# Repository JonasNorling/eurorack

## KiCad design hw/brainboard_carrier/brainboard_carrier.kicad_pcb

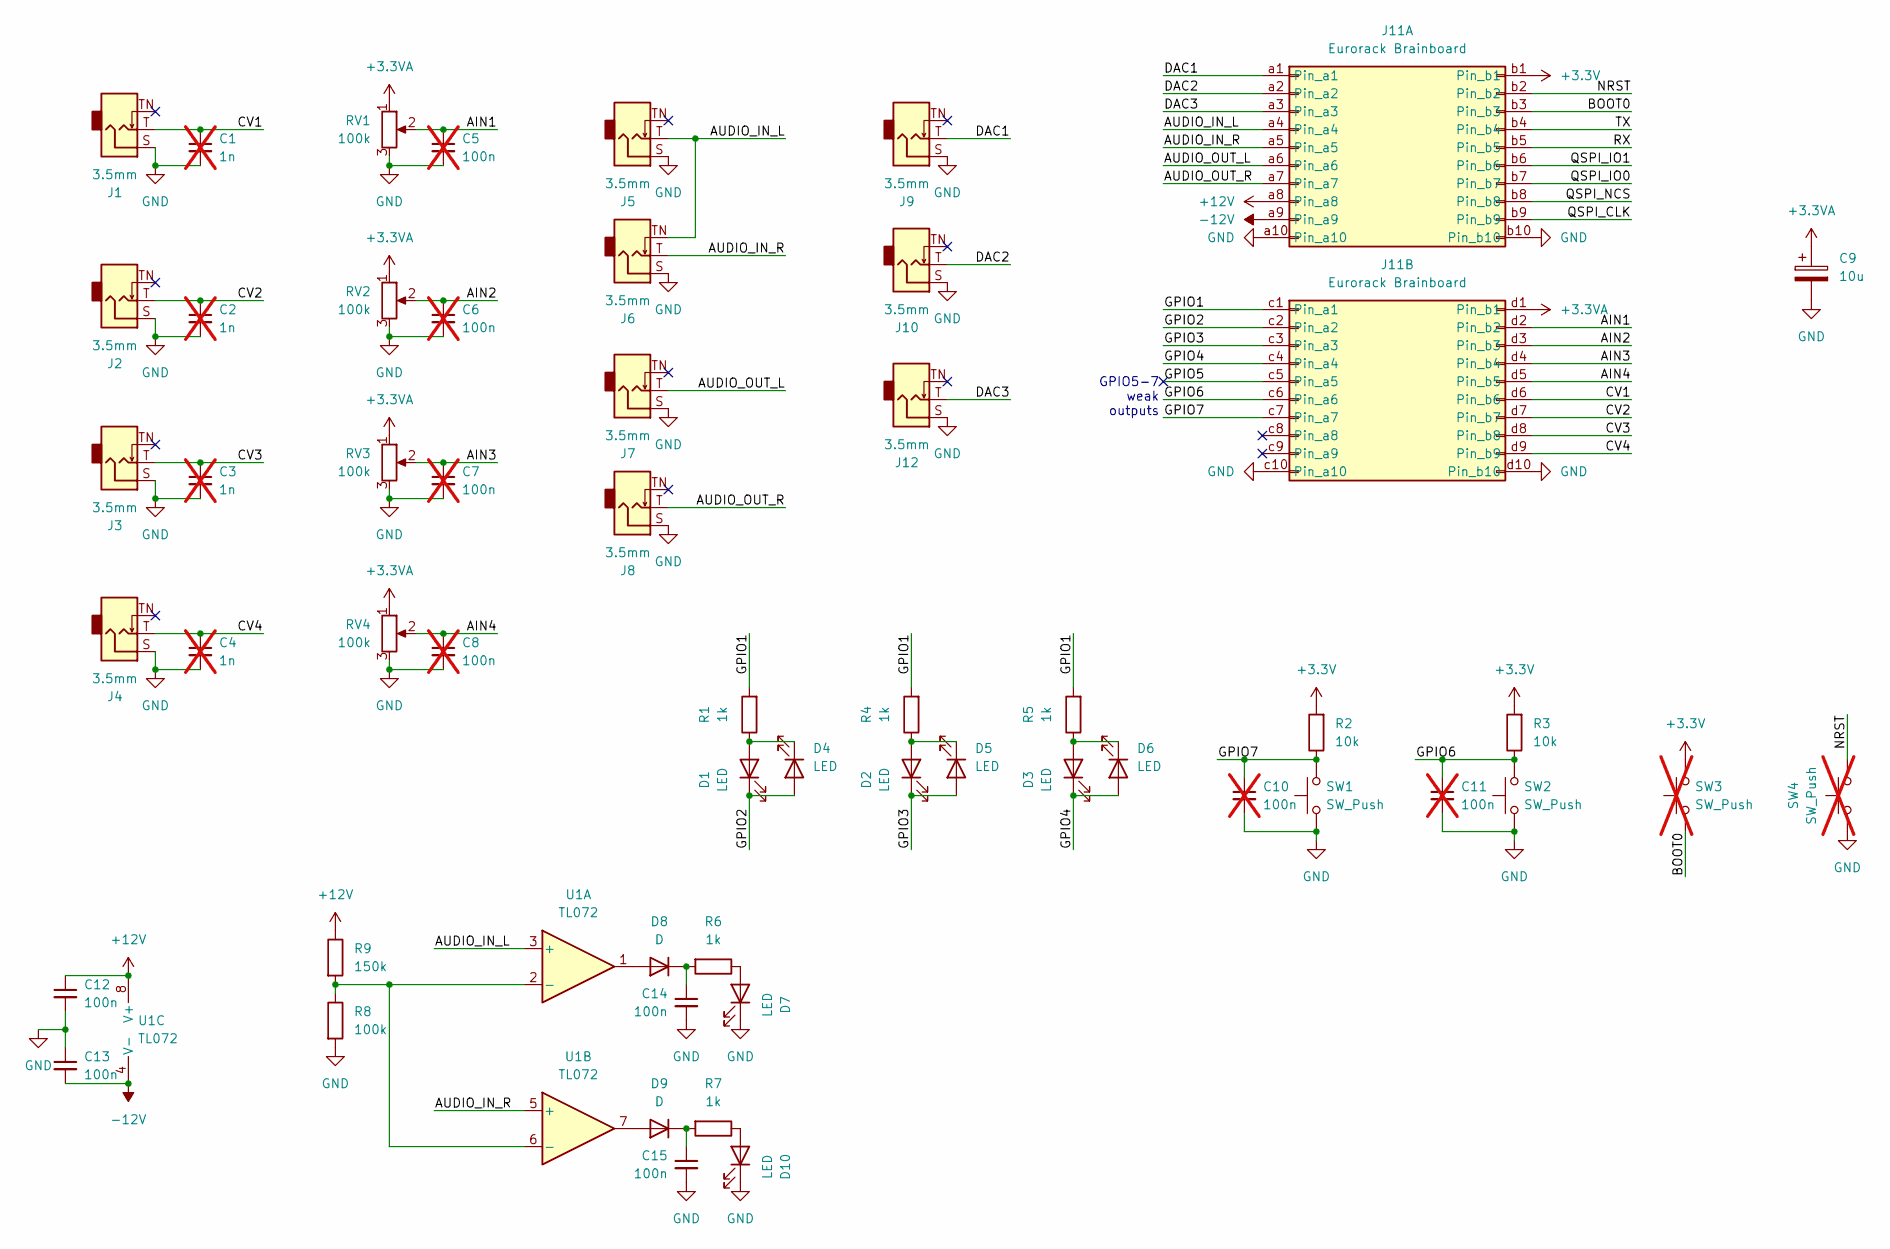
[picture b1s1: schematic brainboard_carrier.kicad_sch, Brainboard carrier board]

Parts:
C1, C2, C3, C4: 1n; C_0603_1608Metric_Pad1.08x0.95mm_HandSolder; not fitted
C5, C6, C7, C8, C10, C11: 100n; C_0603_1608Metric_Pad1.08x0.95mm_HandSolder; not fitted
C9: 10u; C_0805_2012Metric_Pad1.18x1.45mm_HandSolder
C12, C13, C14, C15: 100n; C_0603_1608Metric_Pad1.08x0.95mm_HandSolder
D1, D2, D3, D4, D5, D6, D7, D10: LED; LED_3mm
D8, D9: D; D_SOD-323_HandSoldering; LCSC C2128
J1, J2, J3, J4, J5, J6, J7, J8, J9, J10, J12: 3.5mm; Jack_3.5mm_PJ398SM
J11: Eurorack Brainboard; Brainboard
R1, R4, R5, R6, R7: 1k; R_0603_1608Metric_Pad0.98x0.95mm_HandSolder
R2, R3: 10k; R_0603_1608Metric_Pad0.98x0.95mm_HandSolder
R8: 100k; R_0603_1608Metric_Pad0.98x0.95mm_HandSolder
R9: 150k; R_0603_1608Metric_Pad0.98x0.95mm_HandSolder
RV1, RV2, RV3, RV4: 100k; RV9012NO
SW1, SW2: SW_Push; SW_PUSH_6mm
SW3, SW4: SW_Push; SW_SPST_TS-1088-xR020; LCSC C720477; not fitted
U1: TL072; SOIC-8_3.9x4.9mm_P1.27mm; LCSC C4370389

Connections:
+3.3V: J11.b1, R2.2, R3.2, SW3.2
+3.3VA: C9.1, J11.d1 (Pin_b1), RV1.1, RV2.1, RV3.1, RV4.1
+12V: C12.1, J11.a8, R9.1, U1.8 (V+)
-12V: C13.2, J11.a9, U1.4 (V-)
/AIN1: C5.1, J11.d2 (Pin_b2), RV1.2
/AIN2: C6.1, J11.d3 (Pin_b3), RV2.2
/AIN3: C7.1, J11.d4 (Pin_b4), RV3.2
/AIN4: C8.1, J11.d5 (Pin_b5), RV4.2
/AUDIO_IN_L: J5.T, J6.TN, J11.a4, U1.3 (+)
/AUDIO_IN_R: J6.T, J11.a5, U1.5 (+)
/AUDIO_OUT_L: J7.T, J11.a6
/AUDIO_OUT_R: J8.T, J11.a7
/BOOT0: J11.b3, SW3.1
/CV1: C1.1, J1.T, J11.d6 (Pin_b6)
/CV2: C2.1, J2.T, J11.d7 (Pin_b7)
/CV3: C3.1, J3.T, J11.d8 (Pin_b8)
/CV4: C4.1, J4.T, J11.d9 (Pin_b9)
/DAC1: J9.T, J11.a1
/DAC2: J10.T, J11.a2
/DAC3: J11.a3, J12.T
/GPIO1: J11.c1 (Pin_a1), R1.2, R4.2, R5.2
/GPIO2: D1.1 (K), D4.2 (A), J11.c2 (Pin_a2)
/GPIO3: D2.1 (K), D5.2 (A), J11.c3 (Pin_a3)
/GPIO4: D3.1 (K), D6.2 (A), J11.c4 (Pin_a4)
/GPIO5: J11.c5 (Pin_a5)
/GPIO6: C11.1, J11.c6 (Pin_a6), R3.1, SW2.2
/GPIO7: C10.1, J11.c7 (Pin_a7), R2.1, SW1.2
/NRST: J11.b2, SW4.2
/QSPI_CLK: J11.b9
/QSPI_IO0: J11.b7
/QSPI_IO1: J11.b6
/QSPI_NCS: J11.b8
/RX: J11.b5
/TX: J11.b4
GND: C1.2, C2.2, C3.2, C4.2, C5.2, C6.2, C7.2, C8.2, C9.2, C10.2, C11.2, C12.2, C13.1, C14.2, C15.2, D7.1 (K), D10.1 (K), J1.S, J2.S, J3.S, J4.S, J5.S, J6.S, J7.S, J8.S, J9.S, J10.S, J11.a10, J11.b10, J11.c10 (Pin_a10), J11.d10 (Pin_b10), J12.S, R8.2, RV1.3, RV2.3, RV3.3, RV4.3, SW1.1, SW2.1, SW4.1
unnamed: D1.2 (A), D4.1 (K), R1.1
unnamed: D2.2 (A), D5.1 (K), R4.1
unnamed: D3.2 (A), D6.1 (K), R5.1
unnamed: D7.2 (A), R6.1
unnamed: D8.2 (A), U1.1
unnamed: C14.1, D8.1 (K), R6.2
unnamed: D9.2 (A), U1.7
unnamed: C15.1, D9.1 (K), R7.2
unnamed: D10.2 (A), R7.1
unnamed: R8.1, R9.2, U1.2 (-), U1.6 (-)

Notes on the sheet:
GPIO5-7 weak outputs

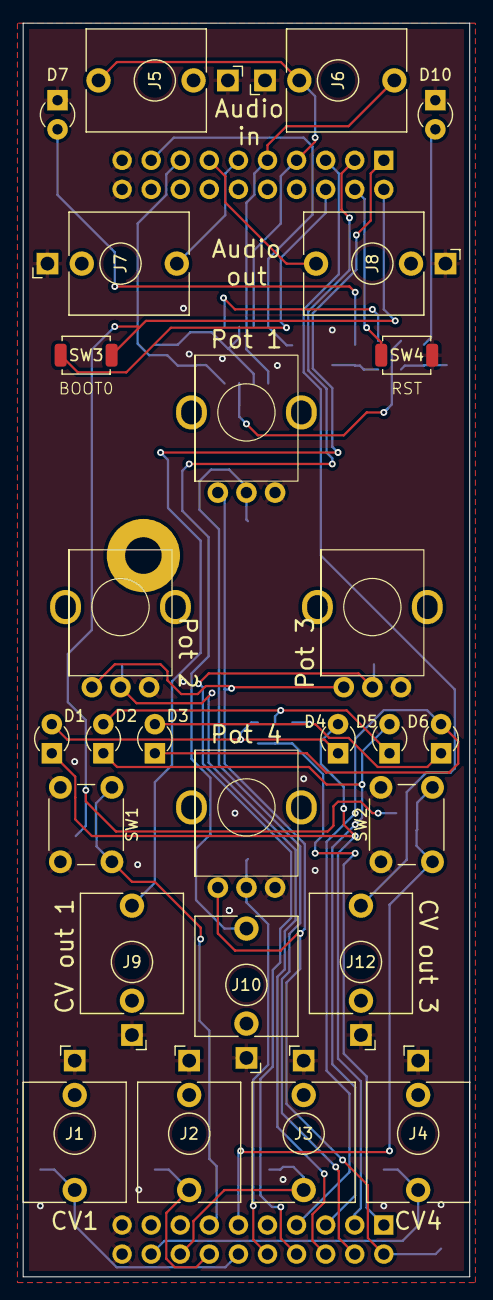
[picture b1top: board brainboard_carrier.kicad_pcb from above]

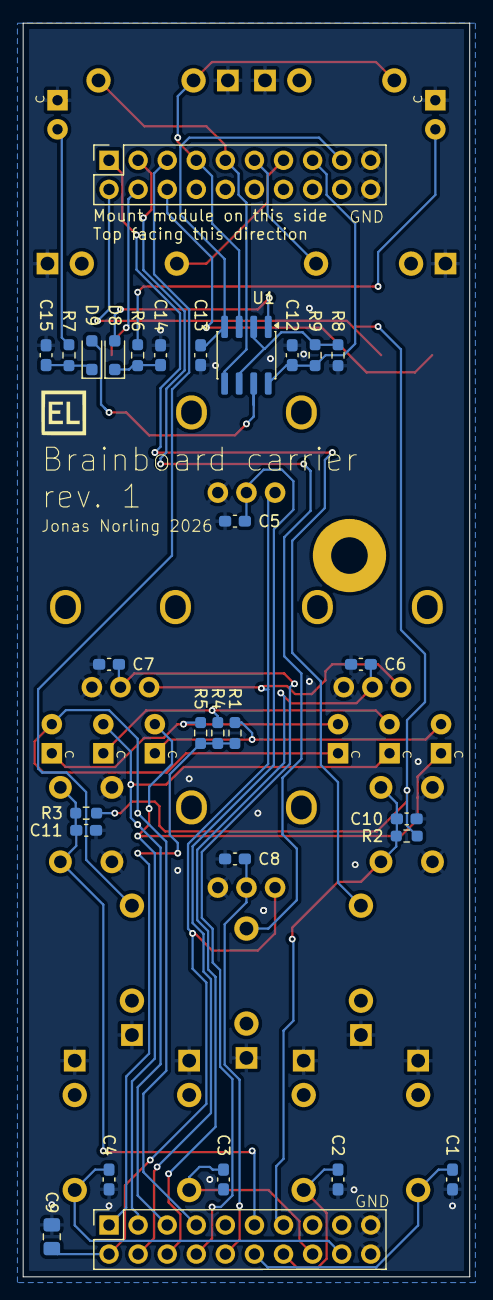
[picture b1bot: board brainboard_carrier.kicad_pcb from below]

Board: 2 copper layers, 39.0 x 109.5 mm, 55 parts (28 on the bottom side), 38 nets.

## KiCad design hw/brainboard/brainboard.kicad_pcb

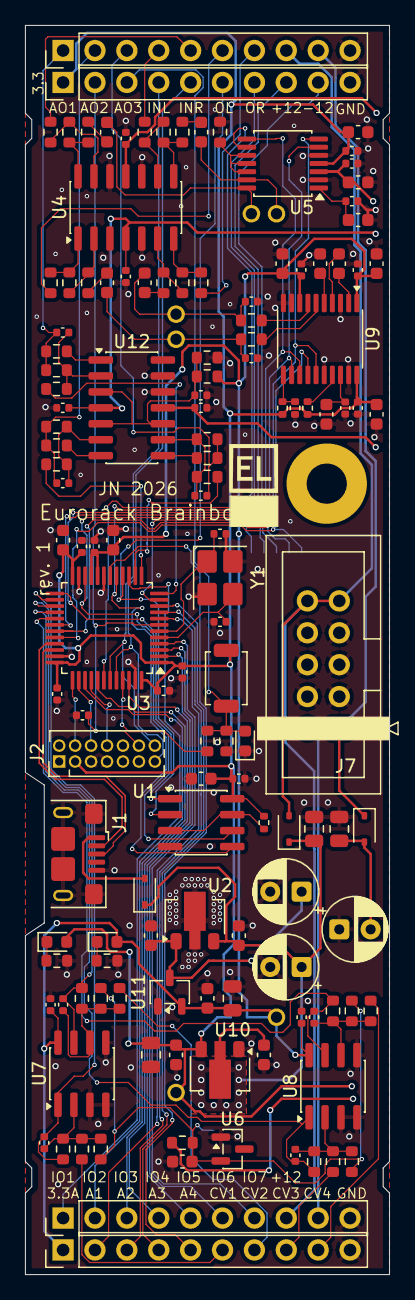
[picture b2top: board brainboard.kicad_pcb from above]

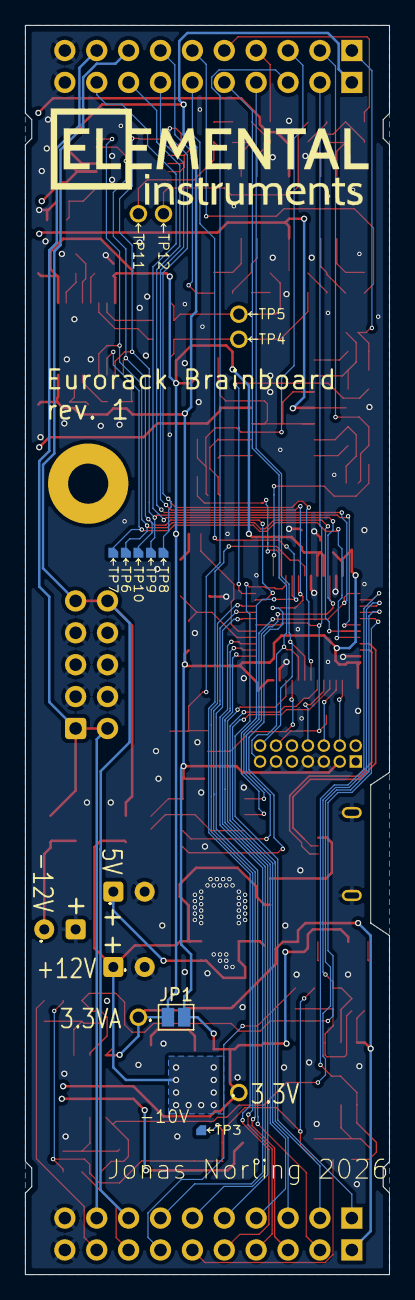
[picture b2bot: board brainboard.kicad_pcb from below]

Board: 4 copper layers, 29.0 x 99.5 mm, 149 parts (11 on the bottom side), 100 nets.

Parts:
C1, C2, C7, C8: 10u; C_0805_2012Metric
C3, C4, C5, C6, C10, C14, C19, C21, C22, C27, C28, C38, C41, C57: 2.2u; C_0603_1608Metric
C9, C11: 20p; C_0402_1005Metric
C12, C13, C15, C16, C17, C18, C23, C24, C30, C31, C40, C43, C45, C47, C51, C53, C55, C56, C58, C59, C61: 100n; C_0402_1005Metric
C20, C62, C63: 10u elyt; CP_Radial_D5.0mm_P2.50mm
C25, C26, C60: 1n; C_0402_1005Metric
C29: 470n; C_0603_1608Metric
C32, C33, C34, C35, C36, C37: 4.7n; C_0402_1005Metric
C39, C42, C44, C46, C50, C52, C54: 10u; C_0603_1608Metric
D1, D2, D3: 1N4007; D_SOD-323
D6, D7, D8: LED; LED_0603_1608Metric
H1: MountingHole; MountingHole_3.2mm_M3_Pad
J1: USB_B_Micro; USB_Micro-B_Amphenol_10118193-0001LF_Horizontal
J2: Conn_ST_STDC14; PinHeader_2x07_P1.27mm_Vertical
J3: gpio; PinHeader_1x10_P2.54mm_Vertical
J4: misc; PinHeader_1x10_P2.54mm_Vertical
J5: inputs; PinHeader_1x10_P2.54mm_Vertical
J6: audio_dac_power; PinHeader_1x10_P2.54mm_Vertical
J7: eurorack_power; IDC-Header_2x05_P2.54mm_Vertical
JP1: tie; SolderJumper-2_P1.3mm_Open_Pad1.0x1.5mm
R3, R4, R14, R15, R16, R17, R18, R33, R34, R39, R41, R45, R50: 1k; R_0603_1608Metric
R5, R36: 10k; R_0603_1608Metric
R6, R7, R12, R13: 15k; R_0603_1608Metric
R8, R9, R10, R11, R19, R20, R21, R22, R43, R46, R47, R49: 100k; R_0603_1608Metric
R23, R24, R25, R26: 200k; R_0603_1608Metric
R27, R28, R29, R30, R40, R42, R44: 33k; R_0603_1608Metric
R31, R32, R35, R37: 0; R_0402_1005Metric
R48: 160k; R_0603_1608Metric
SW1: SW_Push; SW_SPST_TS-1088-xR025
TP1: 3V; TP_0.9mm
TP2: 3VA; TP_0.9mm
TP3: -10V; TP_0.8mm_pad
TP4: DAC_L; TP_0.9mm
TP5: DAC_R; TP_0.9mm
TP6, TP7, TP8, TP9, TP10: I2S; TP_0.8mm_pad
TP11: ADC_L; TP_0.9mm
TP12: ADC_R; TP_0.9mm
U1: APS6404L-3SQRx-SN; SOIC-8_3.9x4.9mm_P1.27mm
U2: L78L05_SOT89; SOT-89-3
U3: STM32G474CCTx; LQFP-48_7x7mm_P0.5mm
U4, U12: TL074; SOIC-14_3.9x8.7mm_P1.27mm
U5: PCM1808; TSSOP-14_4.4x5mm_P0.65mm
U6: LM4040DBZ-10; SOT-23
U7, U8: TLV2372; SOIC-8_3.9x4.9mm_P1.27mm
U9: PCM5102A; TSSOP-20_4.4x6.5mm_P0.65mm
U10: HT7533-1-SOT89; SOT-89-3
U11: XC6206P332MR; SOT-23-3
Y1: 12.288 MHz; Crystal_SMD_3225-4Pin_3.2x2.5mm_Lagom

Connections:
+3.3V: C5.1, C8.1, C14.1, C15.1, C16.1, C17.1, C18.1, C19.1, C46.1, C47.1, C52.1, C53.1, C56.1, D6.2 (A), J2.3 (VCC), J4.1, JP1.2 (B), R31.2, R35.2, R37.2, SW1.2, TP1.1, U1.8 (VDD), U3.1 (VBAT), U3.24 (VDD), U3.36 (VDD), U3.48 (VDD), U5.4 (DVDD), U9.20 (DVDD), U10.3 (VOUT)
+3.3VA: C6.1, C7.1, C10.1, C12.1, C30.1, C31.1, C42.1, C43.1, C44.1, C45.1, D7.2 (A), J5.1, JP1.1 (A), R48.1, TP2.1, U3.20 (VREF+), U3.21 (VDDA), U7.8 (V+), U8.8 (V+), U9.1 (CPVDD), U9.8 (AVDD), U11.2 (VO)
+5V: C54.1, C55.1, C57.1, C63.1, U2.1 (OUT), U5.3 (AVDD), U11.3 (VI)
+12V: C1.1, C3.1, C4.1, C20.1, C23.1, C58.1, D1.1 (K), D2.1 (K), U2.3 (IN), U4.4 (V+), U10.2 (VIN), U12.4 (V+)
-10V_REF: C29.2, R18.1, R23.1, R24.1, R25.1, R26.1, TP3.1, U6.2 (A)
-12V: C2.2, C24.2, C59.2, C62.2, D3.2 (A), R18.2, U4.11 (V-), U12.11 (V-)
/+12V: D2.2 (A), J3.8, J6.8, J7.9, J7.10
/-12V: D3.1 (K), J3.9, J6.9, J7.1, J7.2
/AOUT1: R44.2, U3.12 (PA4)
/AOUT2: R40.2, U3.13 (PA5)
/AOUT3: R42.2, U3.14 (PA6)
/DAC1: C60.2, J6.1, R45.1, R47.1
/DAC2: C26.2, J6.2, R41.1, R43.1
/DAC3: C25.2, J6.3, R46.1, R50.1
/VBUS: D1.2 (A), J1.1 (VBUS)
/analog_io/BIAS: C61.2, R48.2, R49.1, U12.3 (+), U12.5 (+), U12.10 (+)
/analog_io/CV1: J5.6, R19.1
/analog_io/CV2: J5.7, R20.1
/analog_io/CV3: J5.8, R21.1
/analog_io/CV4: J5.9, R22.1
/analog_io/CV_INT1: C32.2, R27.2, U3.26 (PB12), U7.1
/analog_io/CV_INT2: C33.2, R28.2, U3.27 (PB13), U7.7
/analog_io/CV_INT3: C34.2, R29.2, U3.28 (PB14), U8.1
/analog_io/CV_INT4: C35.2, R30.2, U3.29 (PB15), U8.7
/audio_io/ADC_L: C27.2, TP11.1, U5.13 (VINL)
/audio_io/ADC_R: C28.2, TP12.1, U5.14 (VINR)
/audio_io/AUDIO_IN_L: J6.4, R8.2
/audio_io/AUDIO_IN_R: J6.5, R9.2
/audio_io/AUDIO_OUT_L: J6.6, R14.1
/audio_io/AUDIO_OUT_R: J6.7, R15.1
/audio_io/DAC_L: C21.1, C36.1, R33.1, TP4.1
/audio_io/DAC_R: C22.1, C37.1, R34.1, TP5.1
/codec/BCK: TP9.1, U3.30 (PA8), U5.8 (BCK), U9.13 (BCK)
/codec/DIN: TP7.1, U3.32 (PA10), U9.14 (DIN)
/codec/DOUT: TP8.1, U3.42 (PB5), U5.9 (DOUT)
/codec/LRCK: TP6.1, U3.31 (PA9), U5.7 (LRCK), U9.15 (LRCK)
/codec/MCLK: TP10.1, U3.11 (PA3), U5.6 (SCKI), U9.12 (SCK)
/codec/VREF_DECOUPLE: C50.1, C51.1, U5.1 (VREF)
/mcu/AIN1: J5.2, U3.8 (PA0)
/mcu/AIN2: J5.3, U3.9 (PA1)
/mcu/AIN3: J5.4, U3.10 (PA2)
/mcu/AIN4: J5.5, U3.18 (PB2)
/mcu/BOOT0: D8.2 (A), J4.3, R5.2, R39.2, SW1.1
/mcu/GPIO1: J3.1, U3.15 (PA7)
/mcu/GPIO2: J3.2, U3.39 (PA15)
/mcu/GPIO3: J3.3, U3.41 (PB4)
/mcu/GPIO4: J3.4, U3.46 (PB9)
/mcu/GPIO5: J3.5, U3.2 (PC13)
/mcu/GPIO6: J3.6, U3.3 (PC14)
/mcu/GPIO7: J3.7, U3.4 (PC15)
/mcu/NRST: C13.1, J2.12 (~RST), J4.2, U3.7 (PG10)
/mcu/OSC_IN: C9.2, U3.5 (PF0), Y1.3
/mcu/OSC_OUT: C11.1, U3.6 (PF1), Y1.1
/mcu/QSPI_CLK: J4.9, U1.6 (SCLK), U3.22 (PB10)
/mcu/QSPI_IO0: J4.7, U1.5 (SI/SIO0), U3.17 (PB1)
/mcu/QSPI_IO1: J4.6, U1.2 (SO/SIO1), U3.16 (PB0)
/mcu/QSPI_NCS: J4.8, U1.1 (~CE), U3.25 (PB11)
/mcu/RX: J2.13 (VCP_RX), J4.5, U3.44 (PB7)
/mcu/SWCLK: J2.6 (JCLK/SWCLK), U3.38 (PA14)
/mcu/SWDIO: J2.4 (JTMS/SWDIO), U3.37 (PA13)
/mcu/TRACESWO: J2.8 (JTDO/SWO), U3.40 (PB3)
/mcu/TX: J2.14 (VCP_TX), J4.4, U3.43 (PB6)
/mcu/USB_D+: J1.3 (D+), U3.34 (PA12)
/mcu/USB_D-: J1.2 (D-), U3.33 (PA11)
GND: C1.2, C2.1, C3.2, C4.2, C5.2, C6.2, C7.2, C8.2, C9.1, C10.2, C11.2, C12.2, C13.2, C14.2, C15.2, C16.2, C17.2, C18.2, C19.2, C20.2, C23.2, C24.1, C29.1, C30.2, C31.2, C36.2, C37.2, C39.2, C40.2, C41.2, C42.2, C43.2, C44.2, C45.2, C46.2, C47.2, C50.2, C51.2, C52.2, C53.2, C54.2, C55.2, C56.2, C57.2, C58.2, C59.1, C61.1, C62.1, C63.2, D8.1 (K), J1.5 (GND), J1.6 (Shield), J2.5 (GND), J2.7 (GND), J2.11 (GNDDetect), J3.10, J4.10, J5.10, J6.10, J7.3, J7.4, J7.5, J7.6, J7.7, J7.8, R3.2, R4.2, R5.1, R32.1, R36.2, R49.2, U1.4 (VSS), U2.2 (GND), U3.19 (VSSA), U3.23 (VSS), U3.35 (VSS), U3.47 (VSS), U4.3 (+), U4.5 (+), U4.10 (+), U4.12 (+), U5.2 (AGND), U5.5 (DGND), U6.1 (K), U7.3 (+), U7.4 (V-), U7.5 (+), U8.3 (+), U8.4 (V-), U8.5 (+), U9.3 (CPGND), U9.9 (AGND), U9.10 (DEMP), U9.16 (FMT), U9.19 (DGND), U10.1 (GND), U11.1 (GND), U12.12 (+), U12.13 (-), Y1.2 (G), Y1.4 (G)
unnamed: C21.2, R6.2
unnamed: C22.2, R7.2
unnamed: C27.1, R16.1
unnamed: C28.1, R17.2
unnamed: D6.1 (K), R3.1
unnamed: D7.1 (K), R4.1
unnamed: R10.1, R14.2, U4.1
unnamed: R11.1, R15.2, U4.7
unnamed: R12.1, R16.2, U4.8
unnamed: R13.1, R17.1, U4.14
unnamed: R41.2, U12.7
unnamed: R45.2, U12.1
unnamed: R50.2, U12.8
unnamed: R37.1, U1.3 (SIO2), U1.7 (SIO3)
unnamed: R39.1, U3.45 (PB8)
unnamed: R6.1, R10.2, U4.2 (-)
unnamed: R7.1, R11.2, U4.6 (-)
unnamed: R8.1, R12.2, U4.9 (-)
unnamed: R9.1, R13.2, U4.13 (-)
unnamed: R36.1, U5.10 (MD0), U5.11 (MD1), U5.12 (FMT)
unnamed: C32.1, R19.2, R23.2, R27.1, U7.2 (-)
unnamed: C33.1, R20.2, R24.2, R28.1, U7.6 (-)
unnamed: C34.1, R21.2, R25.2, R29.1, U8.2 (-)
unnamed: C35.1, R22.2, R26.2, R30.1, U8.6 (-)
unnamed: C38.2, U9.4 (CAPM)
unnamed: C38.1, U9.2 (CAPP)
unnamed: R31.1, R32.2, U9.11 (FLT)
unnamed: C39.1, C40.1, U9.18 (LDOO)
unnamed: R33.2, U9.6 (OUTL)
unnamed: R34.2, U9.7 (OUTR)
unnamed: C41.1, U9.5 (VNEG)
unnamed: R35.1, U9.17 (XSMT)
unnamed: C60.1, R44.1, R47.2, U12.2 (-)
unnamed: C26.1, R40.1, R43.2, U12.6 (-)
unnamed: C25.1, R42.1, R46.2, U12.9 (-)

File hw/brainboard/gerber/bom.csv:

Reference,Qty,Value,Footprint,LCSC
"C1,C2,C7,C8",4,10u,0805,
"C3,C4,C5,C6,C10,C14,C19,C21,C22,C27,C28,C38,C41,C57",14,2.2u,0603,
"C9,C11",2,20p,0402,
"C12,C13,C15,C16,C17,C18,C23,C24,C30,C31,C40,C43,C45,C47,C51,C53,C55,C56,C58,C59,C61",21,100n,0402,
"C25,C26,C60",3,1n,0402,
C29,1,470n,0603,
"C32,C33,C34,C35,C36,C37",6,4.7n,0402,
"C39,C42,C44,C46,C50,C52,C54",7,10u,0603,
"C48,C49",2,1u,0603,
"D1,D2,D3",3,1N4007,Diode_SMD:D_SOD-323,C2128
"D6,D7,D8",3,LED,0603,C2286
H1,1,MountingHole,Holes:MountingHole_3.2mm_M3_Pad,
J1,1,USB_B_Micro,Connector_USB:USB_Micro-B_Amphenol_10118193-0001LF_Horizontal,C132562
J2,1,Conn_ST_STDC14,Connector_PinHeader_1.27mm:PinHeader_2x07_P1.27mm_Vertical,
J3,1,gpio,Connector_PinHeader_2.54mm:PinHeader_1x10_P2.54mm_Vertical,
J4,1,misc,Connector_PinHeader_2.54mm:PinHeader_1x10_P2.54mm_Vertical,
J5,1,inputs,Connector_PinHeader_2.54mm:PinHeader_1x10_P2.54mm_Vertical,
J6,1,audio_dac_power,Connector_PinHeader_2.54mm:PinHeader_1x10_P2.54mm_Vertical,
J7,1,eurorack_power,Connector_IDC:IDC-Header_2x05_P2.54mm_Vertical,
JP1,1,tie,Jumper:SolderJumper-2_P1.3mm_Open_Pad1.0x1.5mm,
"R3,R4,R14,R15,R16,R17,R18,R33,R34,R39,R41,R45,R50",13,1k,0603,
"R5,R6,R7,R12,R13,R36",6,10k,0603,
"R8,R9,R10,R11",4,39k,0603,
"R19,R20,R21,R22,R43,R46,R47,R49",8,100k,0603,
"R23,R24,R25,R26",4,200k,0603,
"R27,R28,R29,R30,R40,R42,R44",7,33k,0603,
"R31,R35,R37",3,0,0402,
R48,1,160k,0603,
SW1,1,SW_Push,Button_Switch_SMD:SW_SPST_TS-1088-xR025,C720477
U2,1,L78L05_SOT89,Package_TO_SOT_SMD:SOT-89-3,C71136
U3,1,STM32G474CCTx,Package_QFP:LQFP-48_7x7mm_P0.5mm,C730124
"U4,U12",2,TL074,Package_SO:SOIC-14_3.9x8.7mm_P1.27mm,C6964
U5,1,PCM1808,Package_SO:TSSOP-14_4.4x5mm_P0.65mm,C55513
U6,1,LM4040DBZ-10,Package_TO_SOT_SMD:SOT-23,C48031102
"U7,U8",2,TLV2372,Package_SO:SOIC-8_3.9x4.9mm_P1.27mm,C27204
U9,1,PCM5102A,Package_SO:TSSOP-20_4.4x6.5mm_P0.65mm,
U10,1,HT7533-1-SOT89,Package_TO_SOT_SMD:SOT-89-3,C14289
U11,1,XC6206P332MR,Package_TO_SOT_SMD:SOT-23-3,C5446
Y1,1,12.288 MHz,Components:Crystal_SMD_3225-4Pin_3.2x2.5mm_Lagom,C362472

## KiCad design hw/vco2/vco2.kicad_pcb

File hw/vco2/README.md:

# Eurorack Dual VCO

This is a dual voltage controller oscillator (VCO) based on the SSI2131 chip, for Eurorack modular synthesizer systems. In goes a one-volt-per-octave control voltage (CV) and out comes a triangle, saw and square wave. Times two. The second oscillator also has a handy low frequency mode.

## Specs

- Power consumption +12V 60mA, -12V 50mA
- Frequency range without CV input: approx. 12Hz to 1.5kHz
- Selectable low frequency range of second oscillator: approx. 8 Hz to 18 seconds
- Inputs:
  - CV (1 volt per octave) for each oscillator. Second oscillator CV normalled to first.
  - PWM (pulse width modulation) for each oscillator square wave, approx. ±5V
- Pots:
  - Range: 7 octave rough tuning
  - Tune: 5 semitone fine tuning
  - PW: Pulse width for square output, 0-100%
- Outputs:
  - Triangle wave ±5V, DC coupled 1kΩ
  - Saw wave ±5V, DC coupled 1kΩ
  - Square wave ±5V, AC coupled

## Assembly instructions

- Solder the shrouded pin header on the bottom side of the board. You could use a rubber band to hold it down.
- Power it up and check voltages.
- Solder the electrolytic caps on the top side of the board, minding polarity. White stripe and short lead means negative, goes into the hole with round pad. Be sure to keep height below 9mm.
- Solder the trimmer pots to the bottom side of the board. The screw should point away from the chip (not that it matters but it will make the calibration instructions correct). Rev 2 board: watch out for the trimmer lead shorting against the switch later on.
- With the aid of a multimeter in ohms mode, adjust the trimmer pots until you measure 24.3kohm between 2.5V (TP3) and pin 13 on each SSI2131. For me this meant 1.5 turns to the left (out). This is not strictly necessary but will make calibration easier later on.
- Put all the jacks, pots, switch and LEDs in their holes. Short, negative, lead on the LEDs go in the holes with square pads. Remove nut and washer from the pots before installing. The two plastic shaft pots are for PW. Put on the front panel and put a couple of rubber bands around the whole thing to hold everything in position. Then solder down all the pots and jacks and the switch. Do the LEDs last, making sure they are aligned properly. LEDs are heat sensitive, so be swift. Trim the LED leads last.
- Put on the front panel and screw on the nuts. Install knobs. The nuts for the 3.5mm jacks are fiddly and designed to drive you mad.
- Power it up and check that outputs are reasonable: around 10.5Vpp from around 11 to 1.5 kHz. It should be fairly playable already if you managed to adjust the tracking trimmer pots with a multimeter.

### Trimming the tracking

- Connect CV to a trusted keyboard or something. Tune the tracking by playing octaves and adjusting trimmers until it sounds right. Use a tuner (could be a phone app) to preserve mental health.
  - Play a low A and tune it with the range and tuning knobs
  - Play a high A and adjust the trimmer pot. If the high note is too high turn left (out), if it's too low turn right (in).
  - Repeat many times. The lower note will have moved when you turned the trimmer.

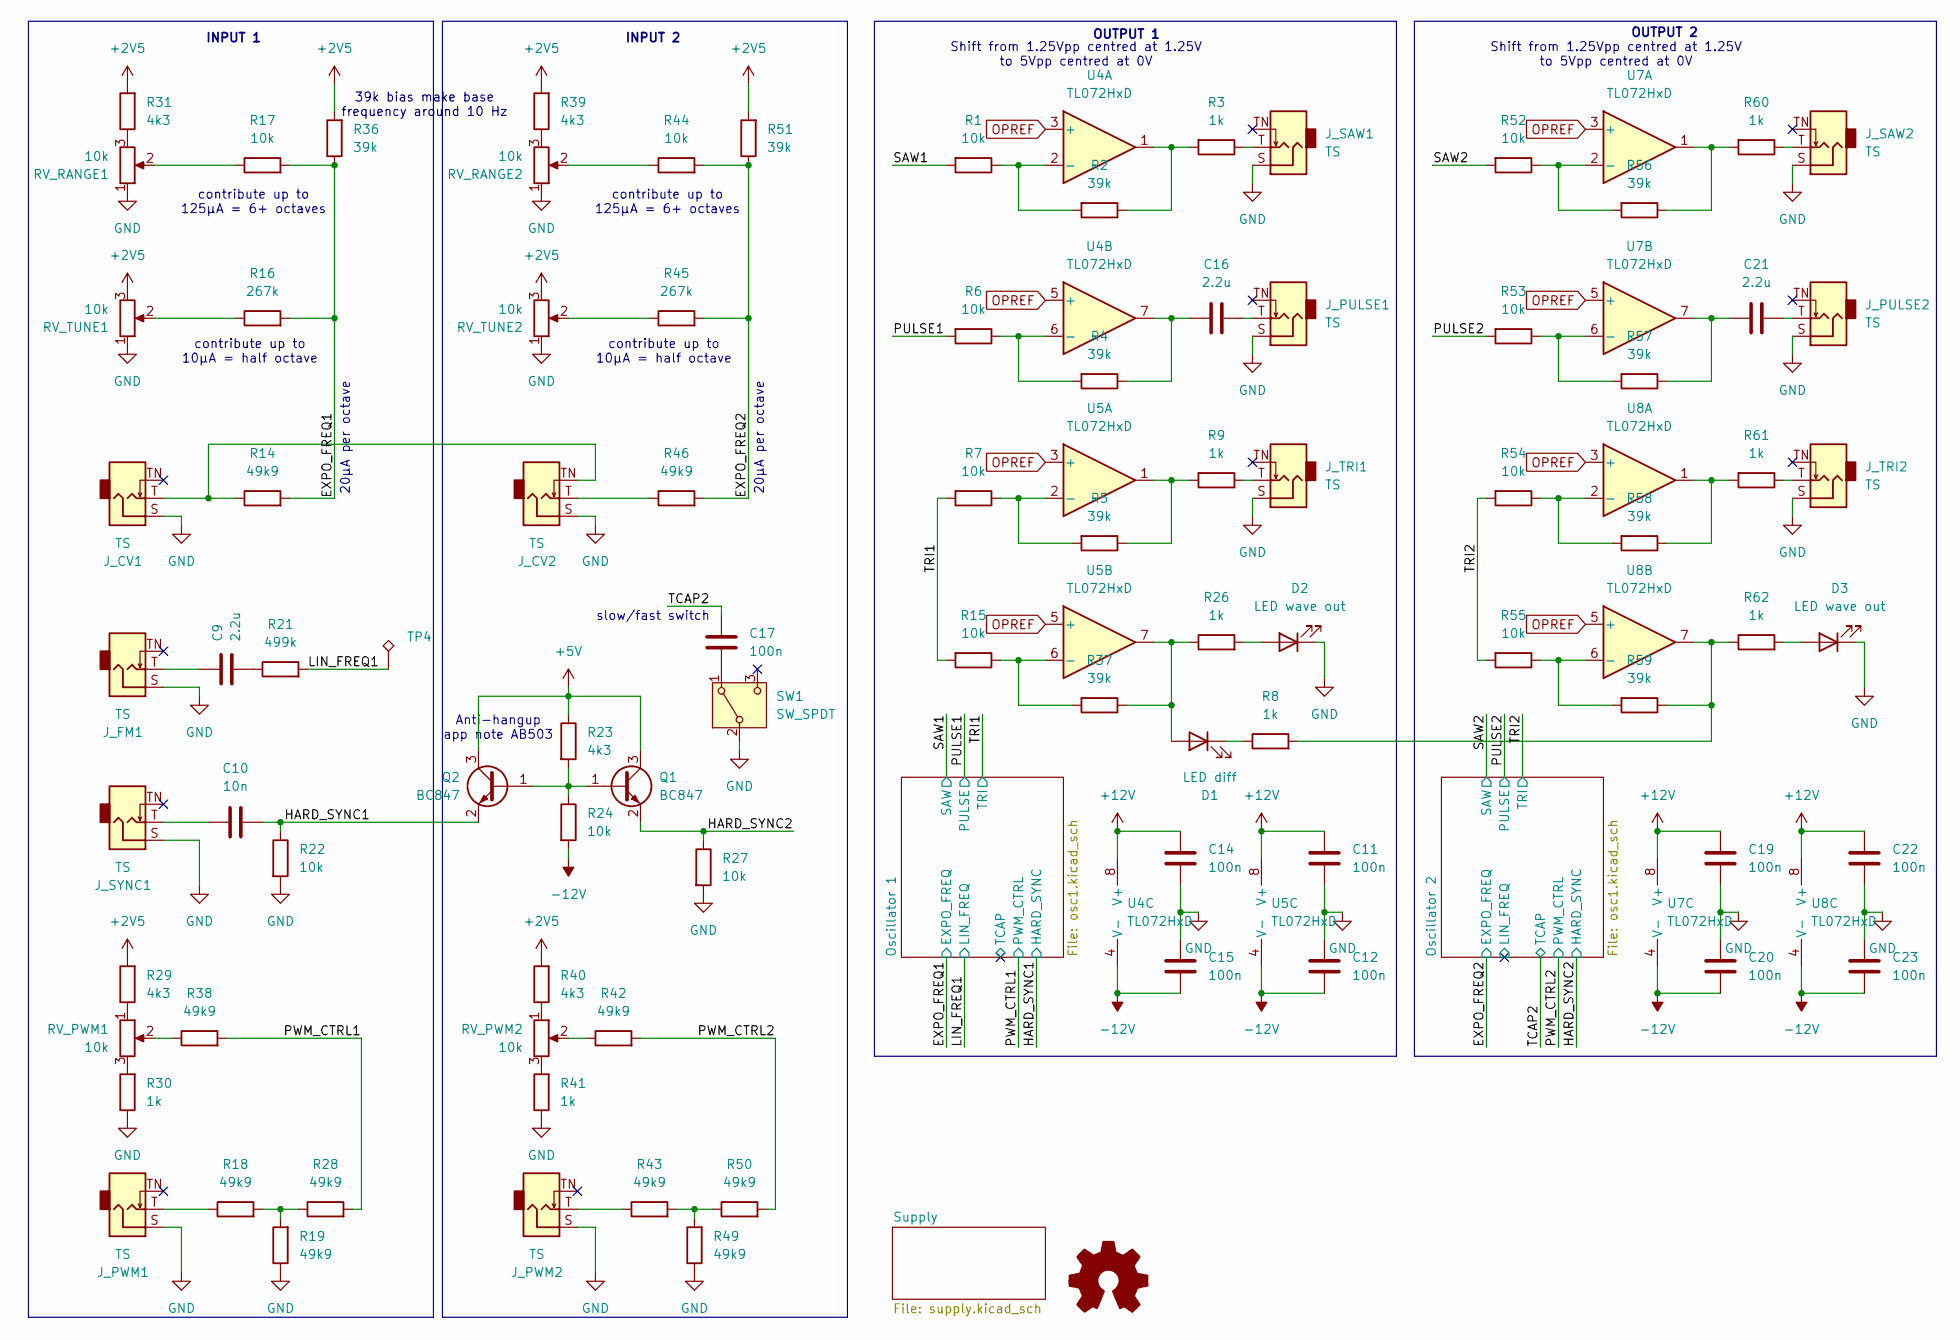
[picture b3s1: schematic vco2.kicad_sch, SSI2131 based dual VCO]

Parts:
C9, C16, C21: 2.2u; C_0805_2012Metric
C10: 10n; C_0603_1608Metric
C11, C12, C14, C15, C17, C19, C20, C22, C23: 100n; C_0603_1608Metric
D1: LED diff; LED_D3.0mm
D2, D3: LED wave out; LED_D3.0mm
J_CV1, J_CV2: TS; Jack_3.5mm_PJ398SM
J_FM1: TS; Jack_3.5mm_PJ398SM
J_PULSE1, J_PULSE2: TS; Jack_3.5mm_PJ398SM
J_PWM1, J_PWM2: TS; Jack_3.5mm_PJ398SM
J_SAW1, J_SAW2: TS; Jack_3.5mm_PJ398SM
J_SYNC1: TS; Jack_3.5mm_PJ398SM
J_TRI1, J_TRI2: TS; Jack_3.5mm_PJ398SM
Q1, Q2: BC847; SOT-23
R1, R6, R7, R15, R17, R22, R24, R27, R44, R52, R53, R54, R55: 10k; R_0603_1608Metric
R2, R4, R5, R36, R37, R51, R56, R57, R58, R59: 39k; R_0603_1608Metric
R3, R8, R9, R26, R30, R41, R60, R61, R62: 1k; R_0603_1608Metric
R14, R18, R19, R28, R38, R42, R43, R46, R49, R50: 49k9; R_0603_1608Metric
R16, R45: 267k; R_0603_1608Metric
R21: 499k; R_0603_1608Metric
R23, R29, R31, R39, R40: 4k3; R_0603_1608Metric
RV_PWM1, RV_PWM2: 10k; RV9012NO
RV_RANGE1, RV_RANGE2: 10k; RV9012NO
RV_TUNE1, RV_TUNE2: 10k; RV9012NO
SW1: SW_SPDT; SPDT big pads
TP4: TestPoint_Alt; TP_0.9mm
U4, U5, U7, U8: TL072HxD; SOIC-8_3.9x4.9mm_P1.27mm; LCSC C4370389

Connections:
+2V5: R29.2, R31.2, R36.2, R39.2, R40.2, R51.2, RV_TUNE1.3, RV_TUNE2.3; also elsewhere on the board
+5V: Q1.3 (C), Q2.3 (C), R23.1; also elsewhere on the board
+12V: C11.1, C14.1, C19.1, C22.1, U4.8 (V+), U5.8 (V+), U7.8 (V+), U8.8 (V+); also elsewhere on the board
-12V: C12.2, C15.2, C20.2, C23.2, R24.2, U4.4 (V-), U5.4 (V-), U7.4 (V-), U8.4 (V-); also elsewhere on the board
/EXPO_FREQ1: R14.2, R16.2, R17.2, R36.1; also elsewhere on the board
/EXPO_FREQ2: R44.2, R45.2, R46.2, R51.1; also elsewhere on the board
/HARD_SYNC1: C10.2, Q2.2 (E), R22.1; also elsewhere on the board
/HARD_SYNC2: Q1.2 (E), R27.1; also elsewhere on the board
/LIN_FREQ1: R21.2, TP4.1; also elsewhere on the board
/PULSE1: R6.2; also elsewhere on the board
/PULSE2: R53.2; also elsewhere on the board
/PWM_CTRL1: R28.2, R38.2; also elsewhere on the board
/PWM_CTRL2: R42.2, R50.2; also elsewhere on the board
/SAW1: R1.2; also elsewhere on the board
/SAW2: R52.2; also elsewhere on the board
/TCAP2: C17.1; also elsewhere on the board
/TRI1: R7.2, R15.2; also elsewhere on the board
/TRI2: R54.2, R55.2; also elsewhere on the board
GND: C11.2, C12.1, C14.2, C15.1, C19.2, C20.1, C22.2, C23.1, D2.1 (K), D3.1 (K), J_CV1.S, J_CV2.S, J_FM1.S, J_PULSE1.S, J_PULSE2.S, J_PWM1.S, J_PWM2.S, J_SAW1.S, J_SAW2.S, J_SYNC1.S, J_TRI1.S, J_TRI2.S, R19.1, R22.2, R27.2, R30.1, R41.1, R49.1, RV_RANGE1.1, RV_RANGE2.1, RV_TUNE1.1, RV_TUNE2.1, SW1.2 (B); also elsewhere on the board
unnamed: C9.1, J_FM1.T
unnamed: C9.2, R21.1
unnamed: C10.1, J_SYNC1.T
unnamed: C16.1, R4.1, U4.7
unnamed: C16.2, J_PULSE1.T
unnamed: C21.1, R57.1, U7.7
unnamed: C21.2, J_PULSE2.T
unnamed: D1.2 (A), R26.1, R37.1, U5.7
unnamed: D1.1 (K), R8.1
unnamed: D2.2 (A), R26.2
unnamed: D3.2 (A), R62.2
unnamed: J_CV1.T, J_CV2.TN, R14.1
unnamed: J_CV2.T, R46.1
unnamed: J_PWM1.T, R18.1
unnamed: J_PWM2.T, R43.1
unnamed: J_SAW1.T, R3.1
unnamed: J_SAW2.T, R60.1
unnamed: J_TRI1.T, R9.1
unnamed: J_TRI2.T, R61.1
unnamed: Q1.1 (B), Q2.1 (B), R23.2, R24.1
unnamed: R2.1, R3.2, U4.1
unnamed: R5.1, R9.2, U5.1
unnamed: R16.1, RV_TUNE1.2
unnamed: R17.1, RV_RANGE1.2
unnamed: R18.2, R19.2, R28.1
unnamed: R29.1, RV_PWM1.1
unnamed: R30.2, RV_PWM1.3
unnamed: R31.1, RV_RANGE1.3
unnamed: R38.1, RV_PWM1.2
unnamed: R39.1, RV_RANGE2.3
unnamed: R40.1, RV_PWM2.1
unnamed: R41.2, RV_PWM2.3
unnamed: R42.1, RV_PWM2.2
unnamed: R43.2, R49.2, R50.1
unnamed: R44.1, RV_RANGE2.2
unnamed: R45.1, RV_TUNE2.2
unnamed: R56.1, R60.2, U7.1
unnamed: R58.1, R61.2, U8.1
unnamed: R8.2, R59.1, R62.1, U8.7
unnamed: C17.2, SW1.1 (A)
unnamed: R1.1, R2.2, U4.2 (-)
unnamed: R4.2, R6.1, U4.6 (-)
unnamed: R5.2, R7.1, U5.2 (-)
unnamed: R15.1, R37.2, U5.6 (-)
unnamed: R52.1, R56.2, U7.2 (-)
unnamed: R53.1, R57.2, U7.6 (-)
unnamed: R54.1, R58.2, U8.2 (-)
unnamed: R55.1, R59.2, U8.6 (-)
OPREF: U4.3 (+), U4.5 (+), U5.3 (+), U5.5 (+), U7.3 (+), U7.5 (+), U8.3 (+), U8.5 (+); also elsewhere on the board

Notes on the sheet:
slow/fast switch
39k bias make base frequency around 10 Hz
contribute up to 125µA = 6+ octaves
contribute up to 10µA = half octave
INPUT 2
20µA per octave
OUTPUT 2
Shift from 1.25Vpp centred at 1.25V to 5Vpp centred at 0V
Anti-hangup app note AB503
INPUT 1
OUTPUT 1

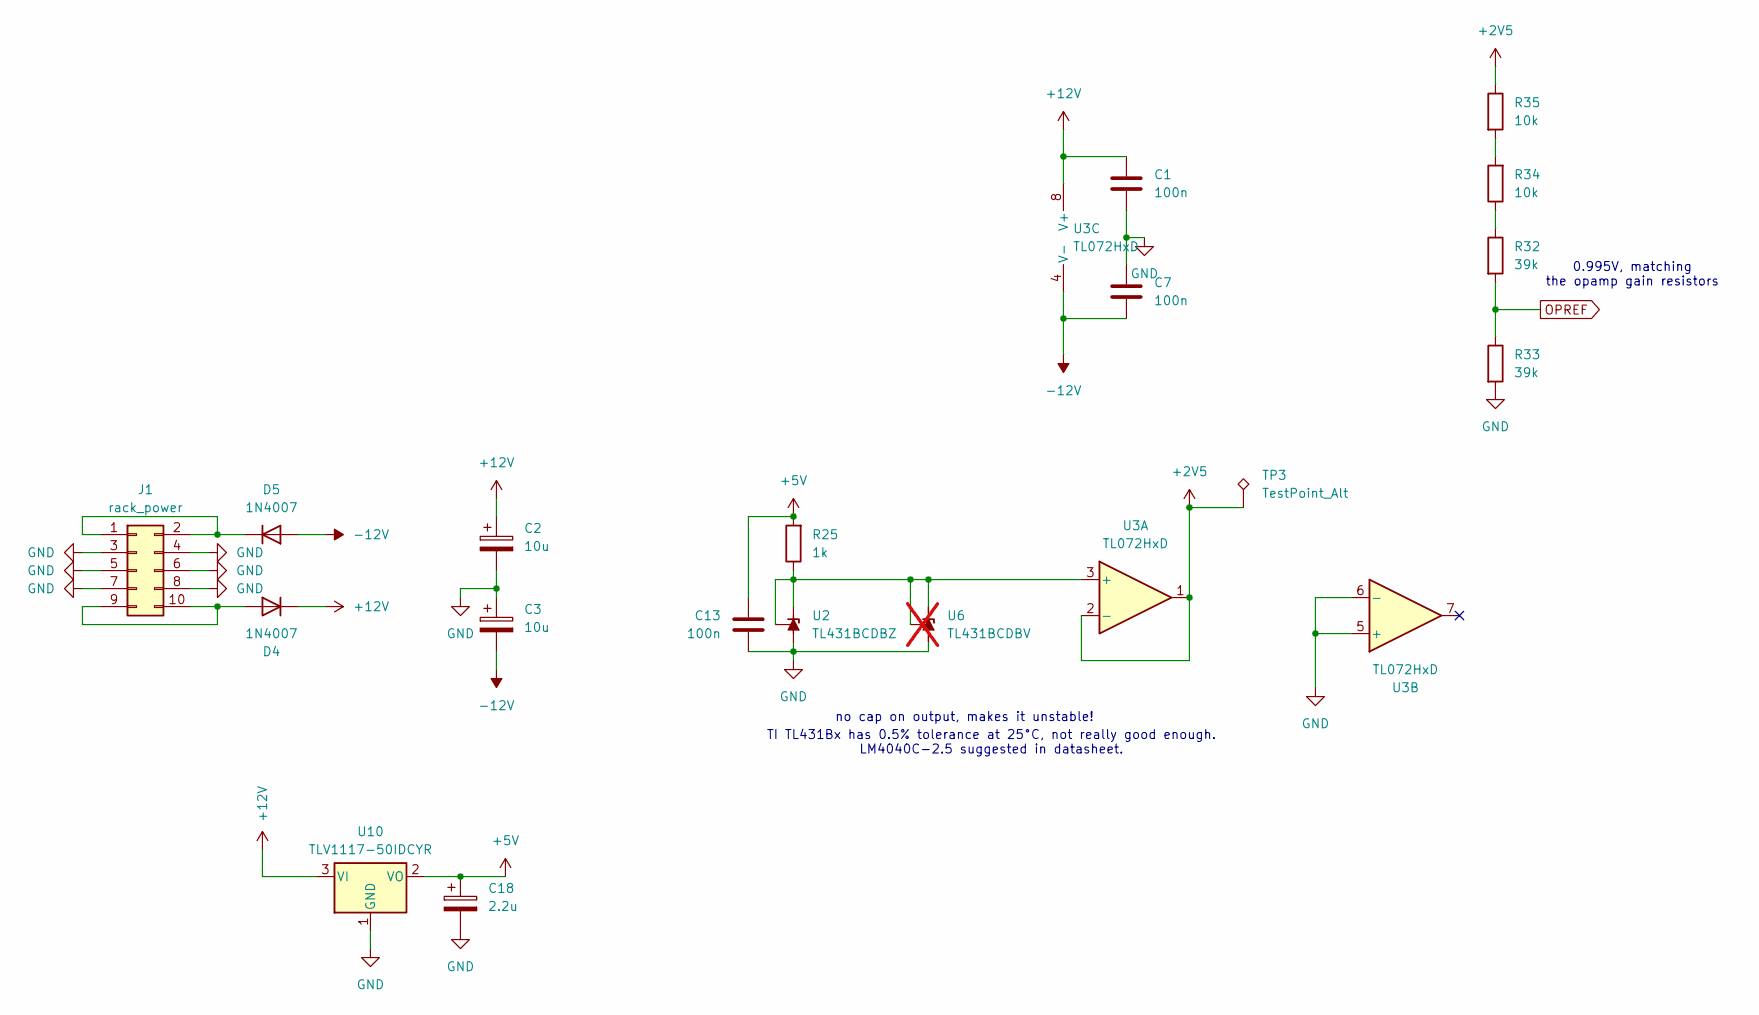
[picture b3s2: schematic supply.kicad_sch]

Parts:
C1, C7, C13: 100n; C_0603_1608Metric
C2, C3: 10u; CP_Radial_D5.0mm_P2.50mm
C18: 2.2u; C_0805_2012Metric
D4, D5: 1N4007; D_SOD-323
J1: rack_power; IDC-Header_2x05_P2.54mm_Vertical
R25: 1k; R_0603_1608Metric
R32, R33: 39k; R_0603_1608Metric
R34, R35: 10k; R_0603_1608Metric
TP3: TestPoint_Alt; TP_0.9mm
U2: TL431BCDBZ; SOT-23; LCSC C6971
U3: TL072HxD; SOIC-8_3.9x4.9mm_P1.27mm; LCSC C4370389
U6: TL431BCDBV; SOT-23-5; not fitted
U10: TLV1117-50IDCYR; SOT-223-3_TabPin2; LCSC C15512

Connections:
+2V5: R35.1, TP3.1, U3.1, U3.2 (-); also elsewhere on the board
+5V: C13.2, C18.1, R25.2, U10.2 (VO); also elsewhere on the board
+12V: C1.1, C2.1, D4.1 (K), U3.8 (V+), U10.3 (VI); also elsewhere on the board
-12V: C3.2, C7.2, D5.2 (A), U3.4 (V-); also elsewhere on the board
GND: C1.2, C2.2, C3.1, C7.1, C13.1, C18.2, J1.3, J1.4, J1.5, J1.6, J1.7, J1.8, R33.2, U2.3 (A), U3.5 (+), U3.6 (-), U6.5 (A), U10.1 (GND); also elsewhere on the board
unnamed: D4.2 (A), J1.9, J1.10
unnamed: D5.1 (K), J1.1, J1.2
unnamed: R32.1, R34.1
unnamed: R34.2, R35.2
unnamed: R25.1, U2.1 (K), U2.2 (REF), U3.3 (+), U6.3 (K), U6.4 (REF)
OPREF: R32.2, R33.1; also elsewhere on the board

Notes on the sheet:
0.995V, matching the opamp gain resistors
no cap on output, makes it unstable!
TI TL431Bx has 0.5% tolerance at 25°C, not really good enough. LM4040C-2.5 suggested in datasheet.
